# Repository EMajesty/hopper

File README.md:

[STM32H743VI](https://www.st.com/resource/en/datasheet/stm32h743vi.pdf)

[PCM3060](https://www.ti.com/lit/ds/symlink/pcm3060.pdf?ts=1771415639587&ref_url=https%253A%252F%252Fwww.ti.com%252Fproduct%252FPCM3060)

[OPA1652](https://www.ti.com/lit/ds/symlink/opa1652.pdf?ts=1771326899051)

[TPS6216x](https://www.ti.com/lit/ds/symlink/tps62160.pdf?ts=1771423545452&ref_url=https%253A%252F%252Fwww.ti.com%252Fproduct%252FTPS62160)

[AMS1117](http://www.advanced-monolithic.com/pdf/ds1117.pdf)

[Omron G5V-2 relay](https://omronfs.omron.com/en_US/ecb/products/pdf/en-g5v_2.pdf)

[Crystal](https://jlcpcb.com/api/file/downloadByFileSystemAccessId/8588976059073646592)

[Tayda 9mm pot](https://www.taydaelectronics.com/datasheets/A-1859.pdf)

[AN4938 - Hardware development](https://www.st.com/resource/en/application_note/an4938-getting-started-with-stm32h74xig-and-stm32h75xig-mcu-hardware-development-stmicroelectronics.pdf)

[AN2867 - Oscillator design](https://www.st.com/resource/en/application_note/cd00221665-oscillator-design-guide-for-stm8af-al-s-stm32-mcus-and-mpus-stmicroelectronics.pdf)

[AN2606 - Memory boot](https://www.st.com/resource/en/application_note/cd00167594-stm32-microcontroller-system-memory-boot-mode-stmicroelectronics.pdf)

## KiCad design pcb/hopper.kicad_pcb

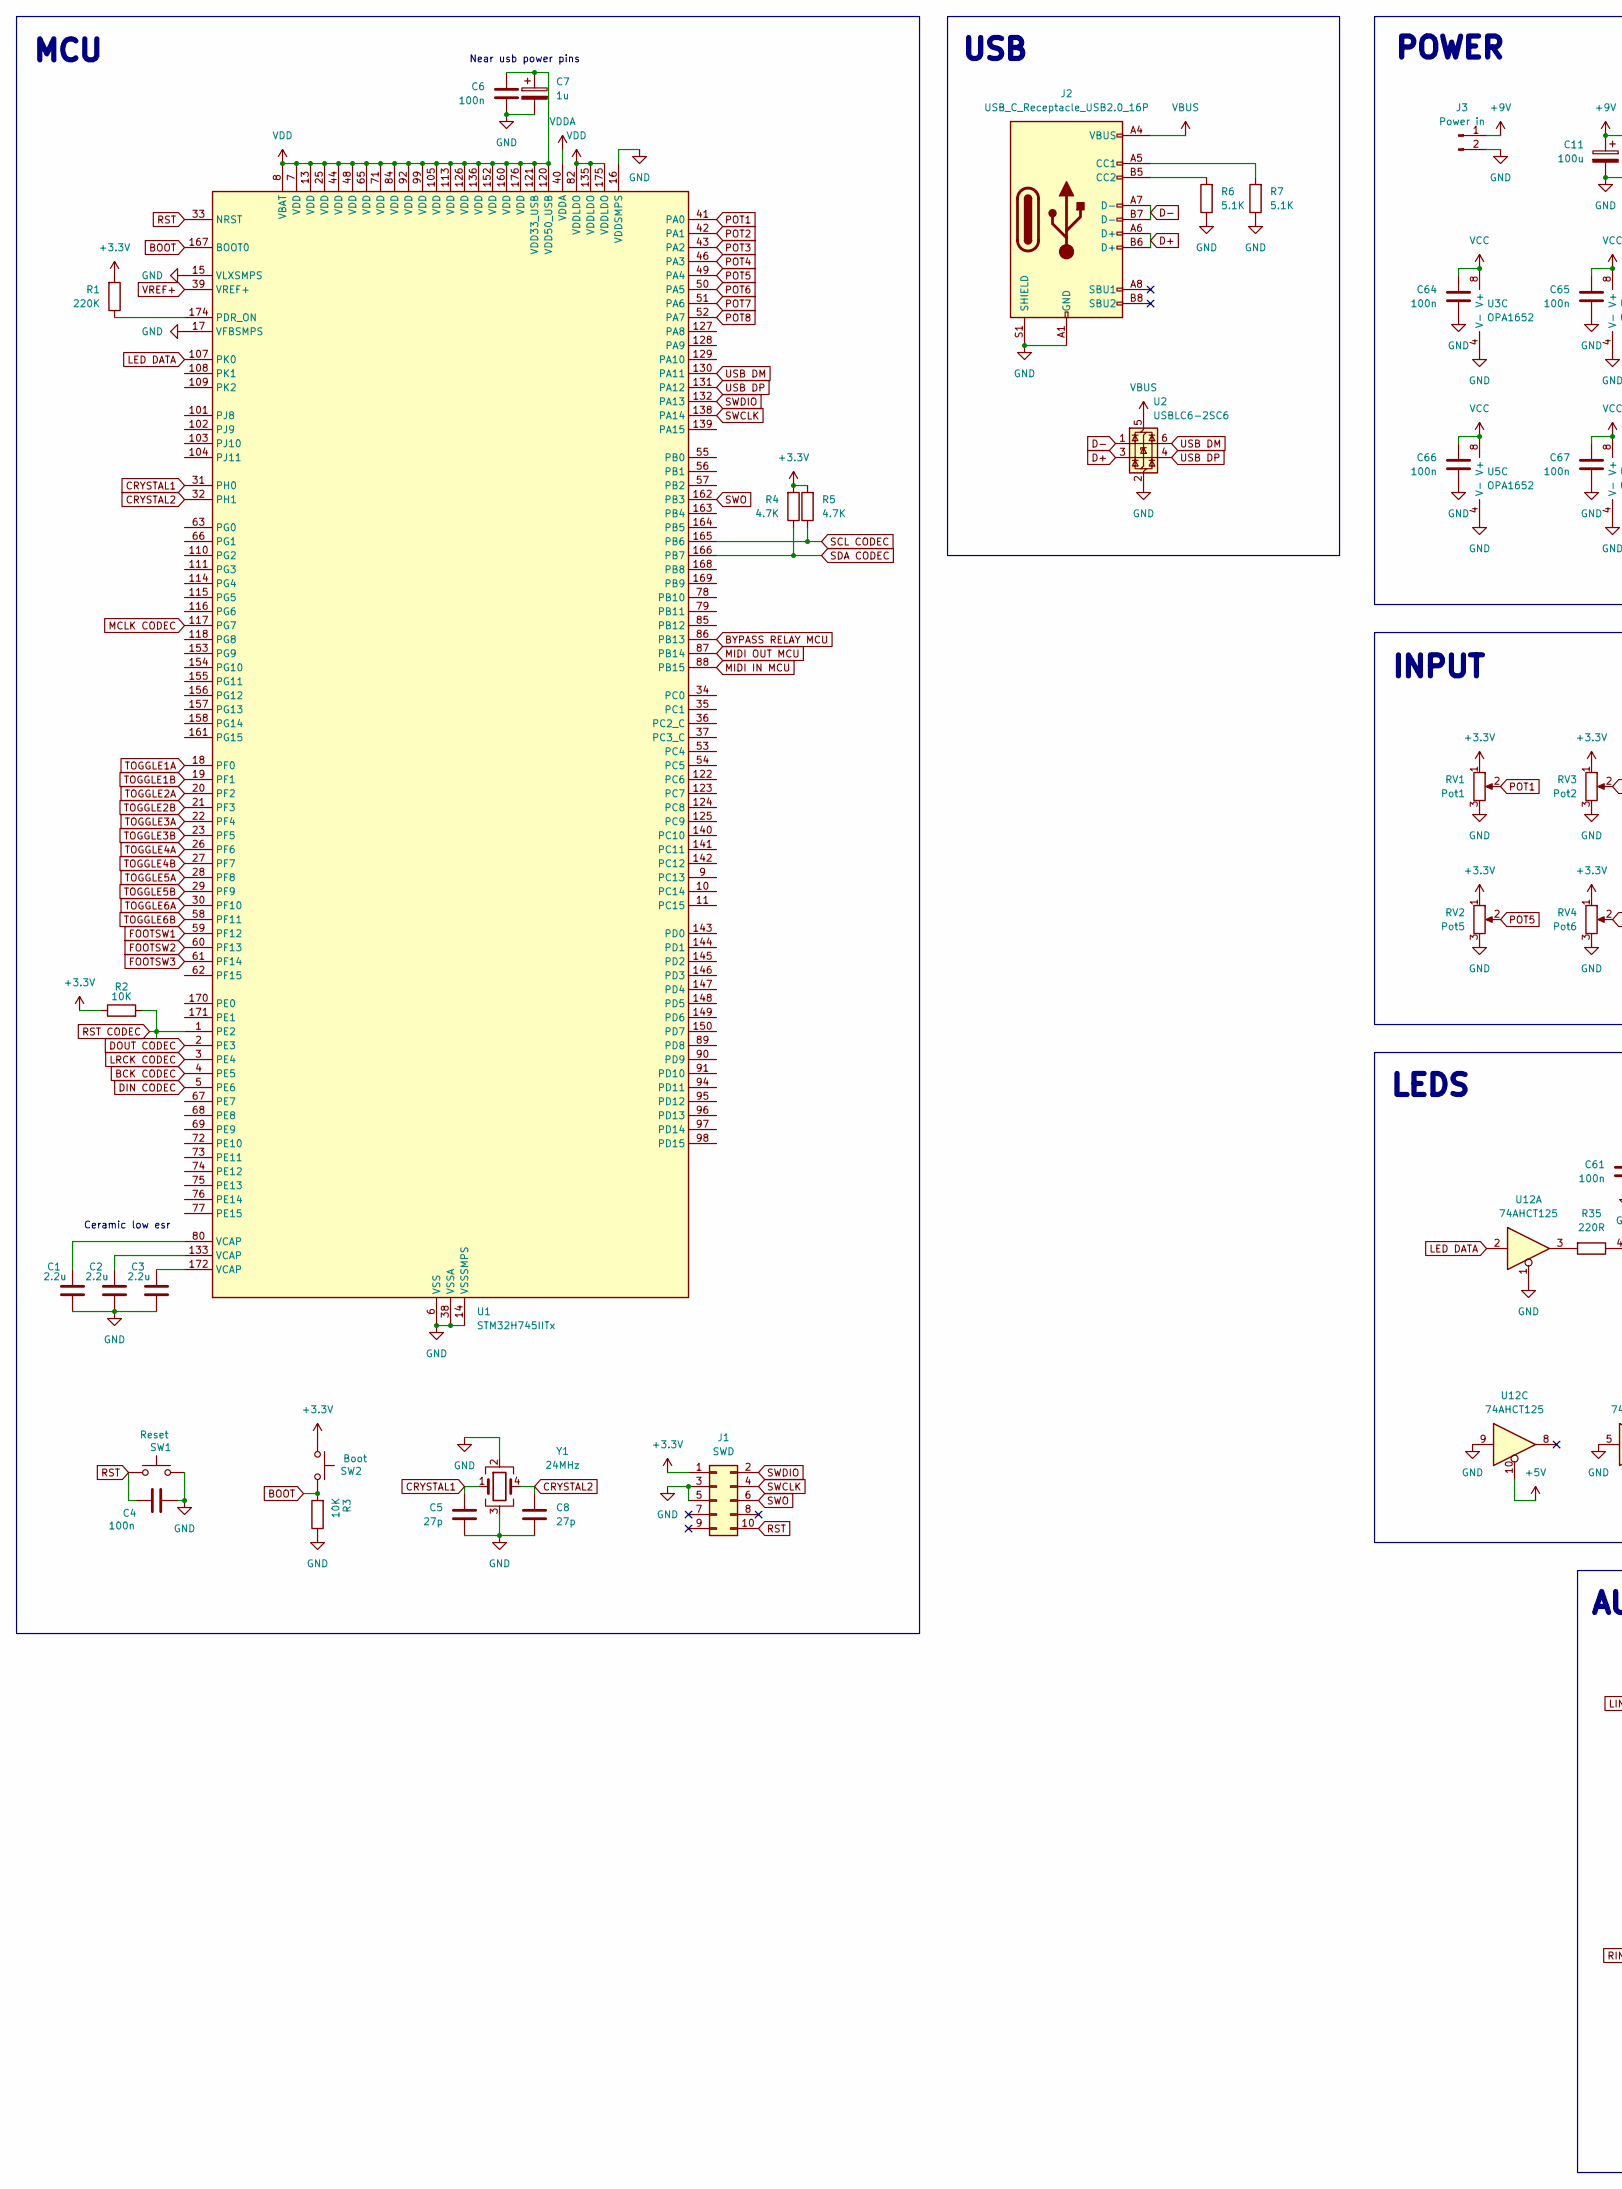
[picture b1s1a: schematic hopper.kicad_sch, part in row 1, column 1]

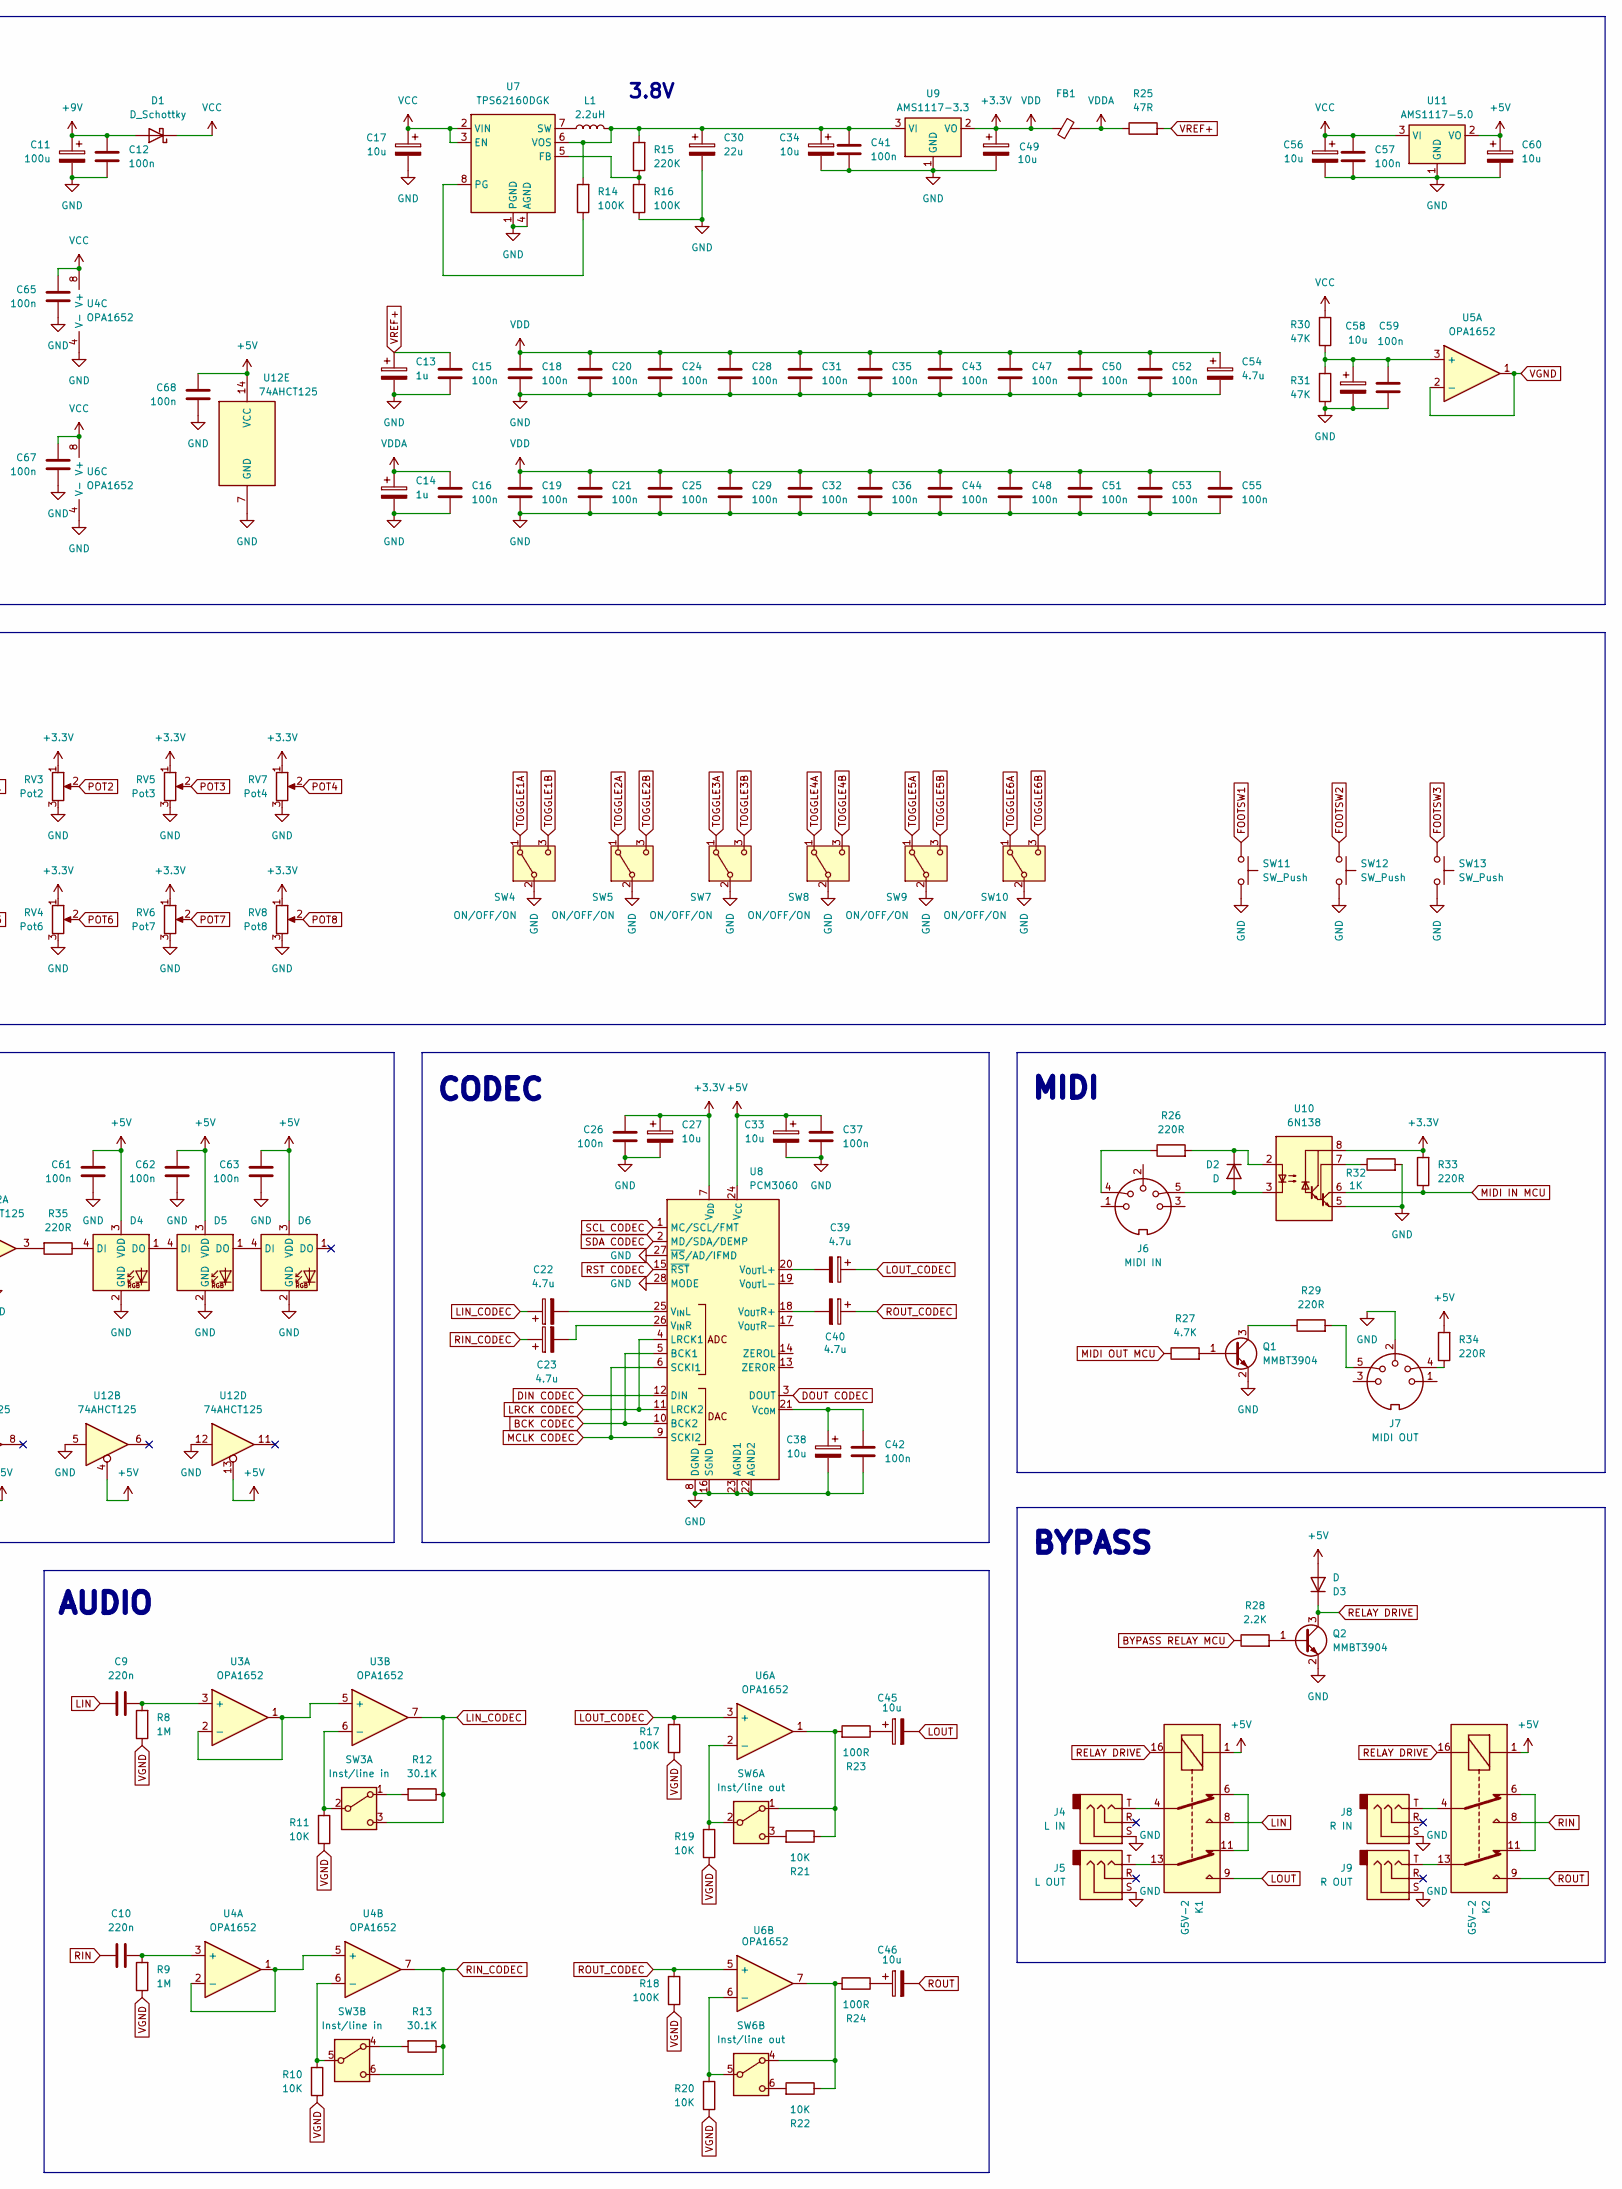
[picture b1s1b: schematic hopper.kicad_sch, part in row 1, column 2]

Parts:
C1, C2, C3: 2.2u; C_0603_1608Metric
C4, C6, C12, C15, C16, C18, C19, C20, C21, C24, C25, C26, C28, C29, C31, C32, C35, C36, C37, C41, C42, C43, C44, C47, C48, C50, C51, C52, C53, C55, C57, C59, C61, C62, C63, C64, C65, C66, C67, C68: 100n; C_0603_1608Metric
C5, C8: 27p; C_0603_1608Metric
C7, C13, C14: 1u; C_0603_1608Metric
C9, C10: 220n; C_0603_1608Metric
C11: 100u; C_0603_1608Metric
C17, C27, C33, C34, C38, C45, C46, C49, C56, C58, C60: 10u; C_0603_1608Metric
C22, C23, C39, C40, C54: 4.7u; C_0603_1608Metric
C30: 22u; C_0805_2012Metric
D1: D_Schottky; D_0603_1608Metric
D2, D3: D; D_0603_1608Metric
D4, D5, D6: APA-106-F5; LED_D5.0mm-4_RGB
FB1: FerriteBead_Small; R_0603_1608Metric
J1: SWD; PinHeader_2x05_P2.54mm_Vertical
J2: USB_C_Receptacle_USB2.0_16P; USB_C_Receptacle_GCT_USB4105-xx-A_16P_TopMnt_Horizontal
J3: Power in; PinHeader_1x02_P2.54mm_Vertical
J4: L IN; Jack_6.35mm_Neutrik_NMJ6HCD2_Horizontal
J5: L OUT; Jack_6.35mm_Neutrik_NMJ6HCD2_Horizontal
J6: MIDI IN
J7: MIDI OUT
J8: R IN; Jack_6.35mm_Neutrik_NMJ6HCD2_Horizontal
J9: R OUT; Jack_6.35mm_Neutrik_NMJ6HCD2_Horizontal
K1, K2: G5V-2; Relay_DPDT_Omron_G5V-2
L1: 2.2uH; R_0603_1608Metric
Q1, Q2: MMBT3904; SOT-23
R1, R15: 220K; R_0603_1608Metric
R2, R3, R10, R11, R19, R20, R21, R22: 10K; R_0603_1608Metric
R4, R5, R27: 4.7K; R_0603_1608Metric
R6, R7: 5.1K; R_0603_1608Metric
R8, R9: 1M; R_0603_1608Metric
R12, R13: 30.1K; R_0603_1608Metric
R14, R16, R17, R18: 100K; R_0603_1608Metric
R23, R24: 100R; R_0603_1608Metric
R25: 47R; R_0603_1608Metric
R26, R29, R33, R34, R35: 220R; R_0603_1608Metric
R28: 2.2K; R_0603_1608Metric
R30, R31: 47K; R_0603_1608Metric
R32: 1K; R_0603_1608Metric
RV1: Pot1; Pot_9mm_DShaft
RV2: Pot5; Pot_9mm_DShaft
RV3: Pot2; Pot_9mm_DShaft
RV4: Pot6; Pot_9mm_DShaft
RV5: Pot3; Pot_9mm_DShaft
RV6: Pot7; Pot_9mm_DShaft
RV7: Pot4; Pot_9mm_DShaft
RV8: Pot8; Pot_9mm_DShaft
SW1: Reset; SW_SPST_TL3342
SW2: Boot; SW_SPST_TL3342
SW3: Inst/line in
SW4, SW5, SW7, SW8, SW9, SW10: ON/OFF/ON; Switch_Toggle_SPDT_Mini_SolderLug
SW6: Inst/line out
SW11, SW12, SW13: SW_Push; PinHeader_1x02_P2.54mm_Vertical
U1: STM32H745IITx; LQFP-176_24x24mm_P0.5mm
U2: USBLC6-2SC6; SOT-23-6
U3, U4, U5, U6: OPA1652; SOIC-8-1EP_3.9x4.9mm_P1.27mm_EP2.29x3mm
U7: TPS62160DGK; MSOP-8_3x3mm_P0.65mm
U8: PCM3060; TSSOP-28_4.4x9.7mm_P0.65mm
U9: AMS1117-3.3; SOT-223-3_TabPin2
U10: 6N138; DIP-8_W7.62mm
U11: AMS1117-5.0; SOT-223-3_TabPin2
U12: 74AHCT125; SOIC-14_3.9x8.7mm_P1.27mm
Y1: 24MHz; Crystal_SMD_3225-4Pin_3.2x2.5mm; JLC C1122380

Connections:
+3.3V: C6.1, C7.1, C18.1, C19.1, C20.1, C21.1, C24.1, C25.1, C26.1, C27.1, C28.1, C29.1, C31.1, C32.1, C35.1, C36.1, C43.1, C44.1, C47.1, C48.1, C49.1, C50.1, C51.1, C52.1, C53.1, C54.1, C55.1, FB1.1, J1.1, R1.2, R2.1, R4.2, R5.2, R33.2, RV1.1, RV2.1, RV3.1, RV4.1, RV5.1, RV6.1, RV7.1, RV8.1, SW2.1, U1.7 (VDD), U1.8 (VBAT), U1.13 (VDD), U1.25 (VDD), U1.44 (VDD), U1.48 (VDD), U1.65 (VDD), U1.71 (VDD), U1.82 (VDDLDO), U1.84 (VDD), U1.92 (VDD), U1.99 (VDD), U1.105 (VDD), U1.113 (VDD), U1.120 (VDD50_USB), U1.121 (VDD33_USB), U1.126 (VDD), U1.135 (VDDLDO), U1.136 (VDD), U1.152 (VDD), U1.160 (VDD), U1.175 (VDDLDO), U1.176 (VDD), U8.7 (V_{DD}), U9.2 (VO), U10.8 (VCC)
+5V: C33.1, C37.1, C60.1, C61.1, C62.1, C63.1, C68.1, D3.2 (A), D4.3 (VDD), D5.3 (VDD), D6.3 (VDD), K1.1, K2.1, R34.2, U8.24 (V_{CC}), U11.2 (VO), U12.4, U12.10, U12.13, U12.14 (VCC)
+9V: C11.1, C12.1, D1.2 (A), J3.1
BCK CODEC: U1.4 (PE5), U8.5 (BCK1), U8.10 (BCK2)
BOOT: R3.2, SW2.2, U1.167 (BOOT0)
BYPASS RELAY MCU: R28.1, U1.86 (PB13)
CRYSTAL1: C5.1, U1.31 (PH0), Y1.1
CRYSTAL2: C8.1, U1.32 (PH1), Y1.4
D+: J2.A6 (D+), J2.B6 (D+), U2.3 (I/O2)
D-: J2.A7 (D-), J2.B7 (D-), U2.1 (I/O1)
DIN CODEC: U1.5 (PE6), U8.12 (DIN)
DOUT CODEC: U1.2 (PE3), U8.3 (DOUT)
FOOTSW1: SW11.1, U1.59 (PF12)
FOOTSW2: SW12.1, U1.60 (PF13)
FOOTSW3: SW13.1, U1.61 (PF14)
GND: C1.2, C2.2, C3.2, C4.2, C5.2, C6.2, C7.2, C8.2, C11.2, C12.2, C13.2, C14.2, C15.2, C16.2, C17.2, C18.2, C19.2, C20.2, C21.2, C24.2, C25.2, C26.2, C27.2, C28.2, C29.2, C30.2, C31.2, C32.2, C33.2, C34.2, C35.2, C36.2, C37.2, C38.2, C41.2, C42.2, C43.2, C44.2, C47.2, C48.2, C49.2, C50.2, C51.2, C52.2, C53.2, C54.2, C55.2, C56.2, C57.2, C58.2, C59.2, C60.2, C61.2, C62.2, C63.2, C64.2, C65.2, C66.2, C67.2, C68.2, D4.2 (GND), D5.2 (GND), D6.2 (GND), J1.3, J1.5, J2.A1 (GND), J2.A12 (GND), J2.B1 (GND), J2.B12 (GND), J2.S1 (SHIELD), J3.2, J4.S, J5.S, J7.2, J8.S, J9.S, Q1.2 (E), Q2.2 (E), R3.1, R6.1, R7.1, R16.1, R31.1, R32.2, RV1.3, RV2.3, RV3.3, RV4.3, RV5.3, RV6.3, RV7.3, RV8.3, SW1.1, SW4.2 (B), SW5.2 (B), SW7.2 (B), SW8.2 (B), SW9.2 (B), SW10.2 (B), SW11.2, SW12.2, SW13.2, U1.6 (VSS), U1.12 (VSS), U1.14 (VSSSMPS), U1.15 (VLXSMPS), U1.16 (VDDSMPS), U1.17 (VFBSMPS), U1.24 (VSS), U1.38 (VSSA), U1.45 (VSS), U1.47 (VSS), U1.64 (VSS), U1.70 (VSS), U1.81 (VSS), U1.83 (VSS), U1.93 (VSS), U1.100 (VSS), U1.106 (VSS), U1.112 (VSS), U1.119 (VSS), U1.134 (VSS), U1.137 (VSS), U1.151 (VSS), U1.159 (VSS), U1.173 (VSS), U2.2 (GND), U3.4 (V-), U4.4 (V-), U5.4 (V-), U6.4 (V-), U7.1 (PGND), U7.4 (AGND), U8.8 (DGND), U8.16 (SGND), U8.22 (AGND2), U8.23 (AGND1), U8.27 (~MS/AD/IFMD), U8.28 (MODE), U9.1 (GND), U10.5 (GND), U11.1 (GND), U12.1, U12.5, U12.7 (GND), U12.9, U12.12, Y1.2, Y1.3
LED DATA: U1.107 (PK0), U12.2
LIN: C9.1, K1.8
LIN_CODEC: C22.1, R12.1, SW3.3 (C), U3.7
LOUT: C45.2, K1.9
LOUT_CODEC: C39.1, R17.2, U6.3 (+)
LRCK CODEC: U1.3 (PE4), U8.4 (LRCK1), U8.11 (LRCK2)
MCLK CODEC: U1.117 (PG7), U8.6 (SCKI1), U8.9 (SCKI2)
MIDI IN MCU: R33.1, U1.88 (PB15), U10.6 (VO2)
MIDI OUT MCU: R27.1, U1.87 (PB14)
unnamed: C1.1, U1.80 (VCAP)
unnamed: C2.1, U1.133 (VCAP)
unnamed: C3.1, U1.172 (VCAP)
unnamed: C45.1, R23.1
unnamed: C46.1, R24.1
unnamed: D2.2 (A), J6.5, U10.3 (C2)
unnamed: D2.1 (K), R26.2, U10.2 (C1)
unnamed: D4.4 (DI), R35.1
unnamed: D4.1 (DO), D5.4 (DI)
unnamed: D5.1 (DO), D6.4 (DI)
unnamed: J2.A5 (CC1), R7.2
unnamed: J2.B5 (CC2), R6.2
unnamed: J4.T, K1.4
unnamed: J5.T, K1.13
unnamed: J6.4, R26.1
unnamed: J7.4, R34.1
unnamed: J7.5, R29.2
unnamed: J8.T, K2.4
unnamed: J9.T, K2.13
unnamed: K1.6, K1.11
unnamed: K2.6, K2.11
unnamed: Q1.1 (B), R27.2
unnamed: Q1.3 (C), R29.1
unnamed: Q2.1 (B), R28.2
unnamed: R35.2, U12.3
unnamed: R12.2, SW3.1 (A)
unnamed: R11.2, SW3.2 (B), U3.6 (-)
unnamed: R13.2, SW3.4 (A)
unnamed: R10.2, SW3.5 (B), U4.6 (-)
unnamed: R21.1, R23.2, SW6.1 (A), U6.1
unnamed: R19.2, SW6.2 (B), U6.2 (-)
unnamed: R21.2, SW6.3 (C)
unnamed: R22.1, R24.2, SW6.4 (A), U6.7
unnamed: R20.2, SW6.5 (B), U6.6 (-)
unnamed: R22.2, SW6.6 (C)
unnamed: R1.1, U1.174 (PDR_ON)
unnamed: C9.2, R8.2, U3.3 (+)
unnamed: U3.1, U3.2 (-), U3.5 (+)
unnamed: C10.2, R9.2, U4.3 (+)
unnamed: U4.1, U4.2 (-), U4.5 (+)
unnamed: C58.1, C59.1, R30.1, R31.2, U5.3 (+)
unnamed: R15.1, R16.2, U7.5 (FB)
unnamed: R14.1, U7.8 (PG)
unnamed: L1.1, U7.7 (SW)
unnamed: C30.1, C34.1, C41.1, L1.2, R14.2, R15.2, U7.6 (VOS), U9.3 (VI)
unnamed: C38.1, C42.1, U8.21 (V_{COM})
unnamed: C22.2, U8.25 (V_{IN}L)
unnamed: C23.2, U8.26 (V_{IN}R)
unnamed: C39.2, U8.20 (V_{OUT}L+)
unnamed: C40.2, U8.18 (V_{OUT}R+)
unnamed: R32.1, U10.7 (VO1)
POT1: RV1.2, U1.41 (PA0)
POT2: RV3.2, U1.42 (PA1)
POT3: RV5.2, U1.43 (PA2)
POT4: RV7.2, U1.46 (PA3)
POT5: RV2.2, U1.49 (PA4)
POT6: RV4.2, U1.50 (PA5)
POT7: RV6.2, U1.51 (PA6)
POT8: RV8.2, U1.52 (PA7)
RELAY DRIVE: D3.1 (K), K1.16, K2.16, Q2.3 (C)
RIN: C10.1, K2.8
RIN_CODEC: C23.1, R13.1, SW3.6 (C), U4.7
ROUT: C46.2, K2.9
ROUT_CODEC: C40.1, R18.2, U6.5 (+)
RST: C4.1, J1.10, SW1.2, U1.33 (NRST)
RST CODEC: R2.2, U1.1 (PE2), U8.15 (~RST)
SCL CODEC: R5.1, U1.165 (PB6), U8.1 (MC/SCL/FMT)
SDA CODEC: R4.1, U1.166 (PB7), U8.2 (MD/SDA/DEMP)
SWCLK: J1.4, U1.138 (PA14)
SWDIO: J1.2, U1.132 (PA13)
SWO: J1.6, U1.162 (PB3)
TOGGLE1A: SW4.1 (A), U1.18 (PF0)
TOGGLE1B: SW4.3 (C), U1.19 (PF1)
TOGGLE2A: SW5.1 (A), U1.20 (PF2)
TOGGLE2B: SW5.3 (C), U1.21 (PF3)
TOGGLE3A: SW7.1 (A), U1.22 (PF4)
TOGGLE3B: SW7.3 (C), U1.23 (PF5)
TOGGLE4A: SW8.1 (A), U1.26 (PF6)
TOGGLE4B: SW8.3 (C), U1.27 (PF7)
TOGGLE5A: SW9.1 (A), U1.28 (PF8)
TOGGLE5B: SW9.3 (C), U1.29 (PF9)
TOGGLE6A: SW10.1 (A), U1.30 (PF10)
TOGGLE6B: SW10.3 (C), U1.58 (PF11)
USB DM: U1.130 (PA11), U2.6 (I/O1)
USB DP: U1.131 (PA12), U2.4 (I/O2)
VBUS: J2.A4 (VBUS), J2.A9 (VBUS), J2.B4 (VBUS), J2.B9 (VBUS), U2.5 (VBUS)
VCC: C17.1, C56.1, C57.1, C64.1, C65.1, C66.1, C67.1, D1.1 (K), R30.2, U3.8 (V+), U4.8 (V+), U5.8 (V+), U6.8 (V+), U7.2 (VIN), U7.3 (EN), U11.3 (VI)
VDDA: C14.1, C16.1, FB1.2, R25.1, U1.40 (VDDA)
VGND: R8.1, R9.1, R10.1, R11.1, R17.1, R18.1, R19.1, R20.1, U5.1, U5.2 (-)
VREF+: C13.1, C15.1, R25.2, U1.39 (VREF+)

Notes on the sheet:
Near usb power pins
MIDI
MCU
INPUT
POWER
CODEC
AUDIO
BYPASS
3.8V
Ceramic low esr
USB
LEDS

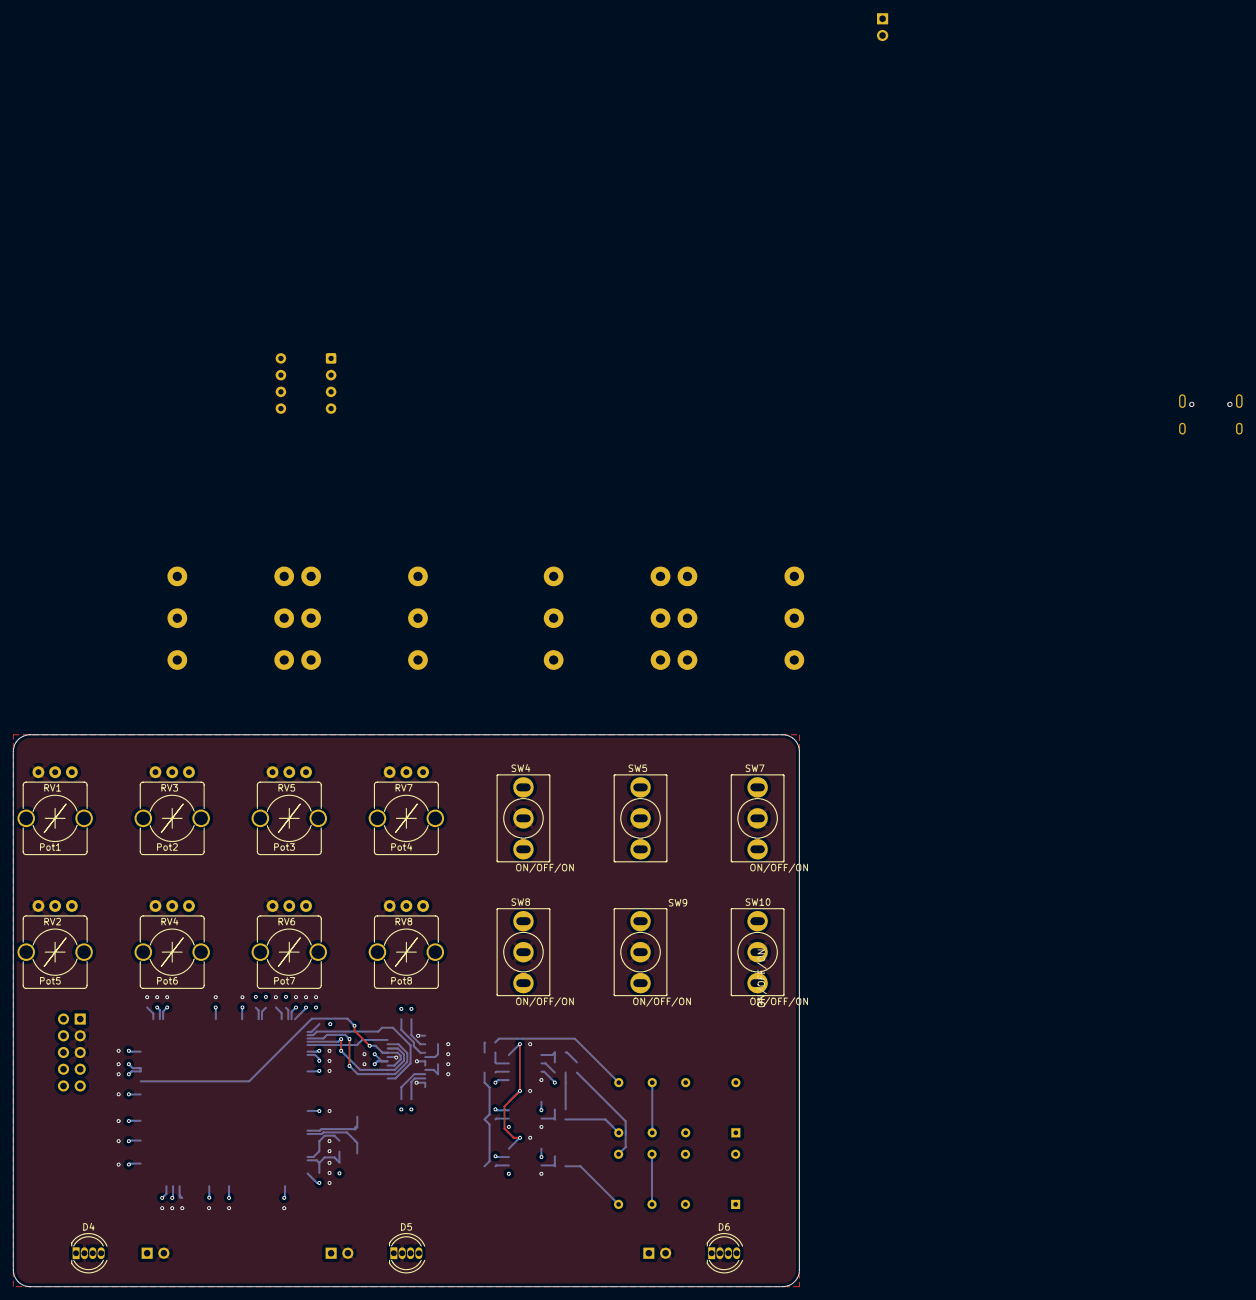
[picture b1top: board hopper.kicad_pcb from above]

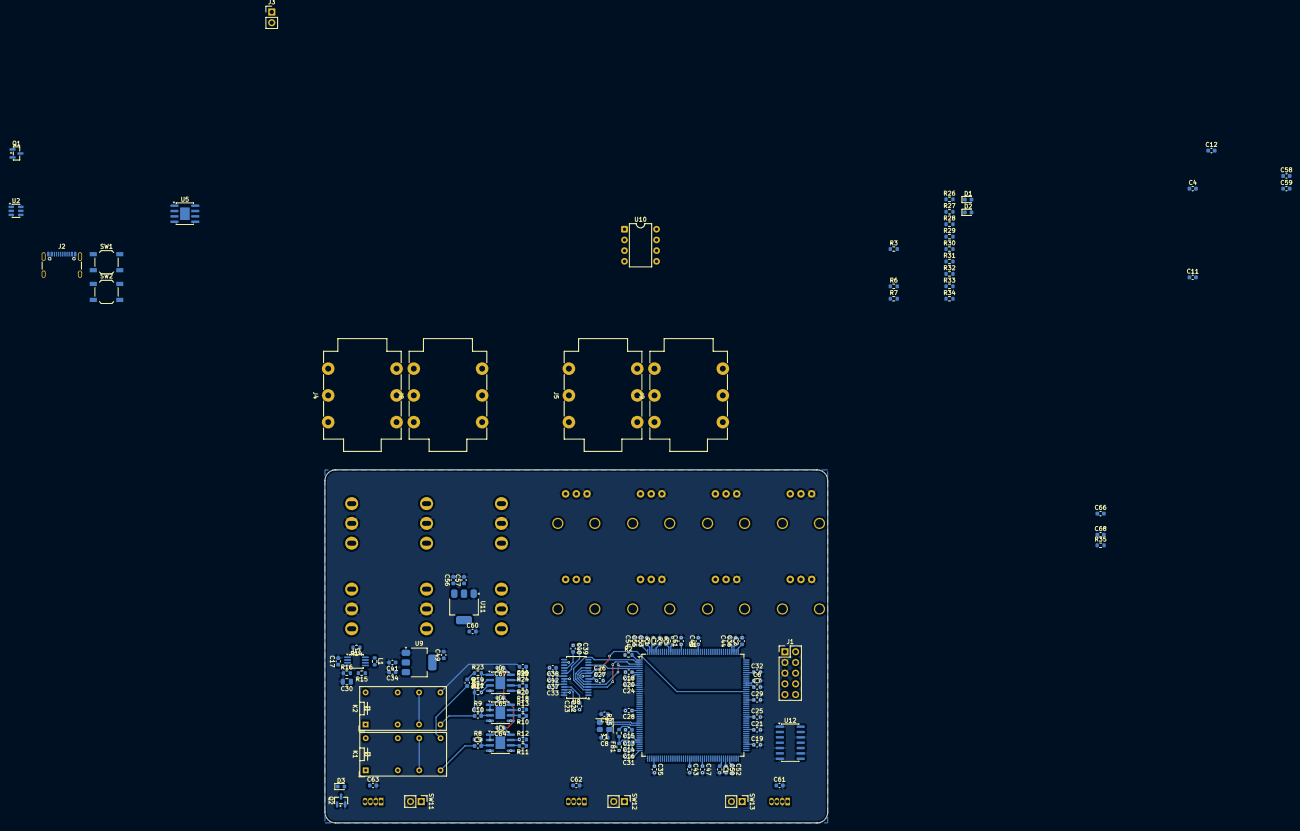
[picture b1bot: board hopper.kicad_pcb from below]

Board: 4 copper layers, 119.4 x 83.8 mm, 154 parts (137 on the bottom side), 108 nets.

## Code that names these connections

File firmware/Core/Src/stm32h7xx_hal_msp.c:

/* USER CODE BEGIN Header */
/**
  ******************************************************************************
  * @file         stm32h7xx_hal_msp.c
  * @brief        This file provides code for the MSP Initialization
  *               and de-Initialization codes.
  ******************************************************************************
  * @attention
  *
  * Copyright (c) 2026 STMicroelectronics.
  * All rights reserved.
  *
  * This software is licensed under terms that can be found in the LICENSE file
  * in the root directory of this software component.
  * If no LICENSE file comes with this software, it is provided AS-IS.
  *
  ******************************************************************************
  */
/* USER CODE END Header */
/* Includes ------------------------------------------------------------------*/
#include "main.h"
/* USER CODE BEGIN Includes */

/* USER CODE END Includes */

/* Private typedef -----------------------------------------------------------*/
/* USER CODE BEGIN TD */

/* USER CODE END TD */

/* Private define ------------------------------------------------------------*/
/* USER CODE BEGIN Define */

/* USER CODE END Define */

/* Private macro -------------------------------------------------------------*/
/* USER CODE BEGIN Macro */

/* USER CODE END Macro */

/* Private variables ---------------------------------------------------------*/
/* USER CODE BEGIN PV */

/* USER CODE END PV */

/* Private function prototypes -----------------------------------------------*/
/* USER CODE BEGIN PFP */

/* USER CODE END PFP */

/* External functions --------------------------------------------------------*/
/* USER CODE BEGIN ExternalFunctions */

/* USER CODE END ExternalFunctions */

/* USER CODE BEGIN 0 */

/* USER CODE END 0 */
/**
  * Initializes the Global MSP.
  */
void HAL_MspInit(void)
{

  /* USER CODE BEGIN MspInit 0 */

  /* USER CODE END MspInit 0 */

  __HAL_RCC_SYSCFG_CLK_ENABLE();

  /* System interrupt init*/

  /* USER CODE BEGIN MspInit 1 */

  /* USER CODE END MspInit 1 */
}

/**
  * @brief ADC MSP Initialization
  * This function configures the hardware resources used in this example
  * @param hadc: ADC handle pointer
  * @retval None
  */
void HAL_ADC_MspInit(ADC_HandleTypeDef* hadc)
{
  GPIO_InitTypeDef GPIO_InitStruct = {0};
  RCC_PeriphCLKInitTypeDef PeriphClkInitStruct = {0};
  if(hadc->Instance==ADC1)
  {
    /* USER CODE BEGIN ADC1_MspInit 0 */

    /* USER CODE END ADC1_MspInit 0 */

  /** Initializes the peripherals clock
  */
    PeriphClkInitStruct.PeriphClockSelection = RCC_PERIPHCLK_ADC;
    PeriphClkInitStruct.PLL2.PLL2M = 2;
    PeriphClkInitStruct.PLL2.PLL2N = 40;
    PeriphClkInitStruct.PLL2.PLL2P = 6;
    PeriphClkInitStruct.PLL2.PLL2Q = 2;
    PeriphClkInitStruct.PLL2.PLL2R = 2;
    PeriphClkInitStruct.PLL2.PLL2RGE = RCC_PLL2VCIRANGE_3;
    PeriphClkInitStruct.PLL2.PLL2VCOSEL = RCC_PLL2VCOWIDE;
    PeriphClkInitStruct.PLL2.PLL2FRACN = 0.0;
    PeriphClkInitStruct.AdcClockSelection = RCC_ADCCLKSOURCE_PLL2;
    if (HAL_RCCEx_PeriphCLKConfig(&PeriphClkInitStruct) != HAL_OK)
    {
      Error_Handler();
    }

    /* Peripheral clock enable */
    __HAL_RCC_ADC12_CLK_ENABLE();

    __HAL_RCC_GPIOC_CLK_ENABLE();
    __HAL_RCC_GPIOA_CLK_ENABLE();
    __HAL_RCC_GPIOB_CLK_ENABLE();
    /**ADC1 GPIO Configuration
    PC0     ------> ADC1_INP10
    PC1     ------> ADC1_INP11
    PA0     ------> ADC1_INP16
    PA1     ------> ADC1_INP17
    PA2     ------> ADC1_INP14
    PA3     ------> ADC1_INP15
    PA4     ------> ADC1_INP18
    PA5     ------> ADC1_INP19
    PA6     ------> ADC1_INP3
    PA7     ------> ADC1_INP7
    PC4     ------> ADC1_INP4
    PC5     ------> ADC1_INP8
    PB0     ------> ADC1_INP9
    PB1     ------> ADC1_INP5
    */
    GPIO_InitStruct.Pin = GPIO_PIN_0|GPIO_PIN_1|GPIO_PIN_4|GPIO_PIN_5;
    GPIO_InitStruct.Mode = GPIO_MODE_ANALOG;
    GPIO_InitStruct.Pull = GPIO_PULLDOWN;
    HAL_GPIO_Init(GPIOC, &GPIO_InitStruct);

    GPIO_InitStruct.Pin = GPIO_PIN_0|GPIO_PIN_1|GPIO_PIN_2|GPIO_PIN_3
                          |GPIO_PIN_4|GPIO_PIN_5|GPIO_PIN_6|GPIO_PIN_7;
    GPIO_InitStruct.Mode = GPIO_MODE_ANALOG;
    GPIO_InitStruct.Pull = GPIO_NOPULL;
    HAL_GPIO_Init(GPIOA, &GPIO_InitStruct);

    GPIO_InitStruct.Pin = GPIO_PIN_0|GPIO_PIN_1;
    GPIO_InitStruct.Mode = GPIO_MODE_ANALOG;
    GPIO_InitStruct.Pull = GPIO_PULLDOWN;
    HAL_GPIO_Init(GPIOB, &GPIO_InitStruct);

    /* USER CODE BEGIN ADC1_MspInit 1 */

    /* USER CODE END ADC1_MspInit 1 */

  }

}

/**
  * @brief ADC MSP De-Initialization
  * This function freeze the hardware resources used in this example
  * @param hadc: ADC handle pointer
  * @retval None
  */
void HAL_ADC_MspDeInit(ADC_HandleTypeDef* hadc)
{
  if(hadc->Instance==ADC1)
  {
    /* USER CODE BEGIN ADC1_MspDeInit 0 */

    /* USER CODE END ADC1_MspDeInit 0 */
    /* Peripheral clock disable */
    __HAL_RCC_ADC12_CLK_DISABLE();

    /**ADC1 GPIO Configuration
    PC0     ------> ADC1_INP10
    PC1     ------> ADC1_INP11
    PA0     ------> ADC1_INP16
    PA1     ------> ADC1_INP17
    PA2     ------> ADC1_INP14
    PA3     ------> ADC1_INP15
    PA4     ------> ADC1_INP18
    PA5     ------> ADC1_INP19
    PA6     ------> ADC1_INP3
    PA7     ------> ADC1_INP7
    PC4     ------> ADC1_INP4
    PC5     ------> ADC1_INP8
    PB0     ------> ADC1_INP9
    PB1     ------> ADC1_INP5
    */
    HAL_GPIO_DeInit(GPIOC, GPIO_PIN_0|GPIO_PIN_1|GPIO_PIN_4|GPIO_PIN_5);

    HAL_GPIO_DeInit(GPIOA, GPIO_PIN_0|GPIO_PIN_1|GPIO_PIN_2|GPIO_PIN_3
                          |GPIO_PIN_4|GPIO_PIN_5|GPIO_PIN_6|GPIO_PIN_7);

    HAL_GPIO_DeInit(GPIOB, GPIO_PIN_0|GPIO_PIN_1);

    /* USER CODE BEGIN ADC1_MspDeInit 1 */

    /* USER CODE END ADC1_MspDeInit 1 */
  }

}

static uint32_t SAI1_client =0;

void HAL_SAI_MspInit(SAI_HandleTypeDef* hsai)
{

  GPIO_InitTypeDef GPIO_InitStruct;
/* SAI1 */
    if(hsai->Instance==SAI1_Block_A)
    {
    /* Peripheral clock enable */
    if (SAI1_client == 0)
    {
       __HAL_RCC_SAI1_CLK_ENABLE();
    }
    SAI1_client ++;

    /**SAI1_A_Block_A GPIO Configuration
    PE2     ------> SAI1_MCLK_A
    PE4     ------> SAI1_FS_A
    PE5     ------> SAI1_SCK_A
    PE6     ------> SAI1_SD_A
    */
    GPIO_InitStruct.Pin = GPIO_PIN_2|GPIO_PIN_4|GPIO_PIN_5|GPIO_PIN_6;
    GPIO_InitStruct.Mode = GPIO_MODE_AF_PP;
    GPIO_InitStruct.Pull = GPIO_NOPULL;
    GPIO_InitStruct.Speed = GPIO_SPEED_FREQ_LOW;
    GPIO_InitStruct.Alternate = GPIO_AF6_SAI1;
    HAL_GPIO_Init(GPIOE, &GPIO_InitStruct);

    }
    if(hsai->Instance==SAI1_Block_B)
    {
      /* Peripheral clock enable */
      if (SAI1_client == 0)
      {
       __HAL_RCC_SAI1_CLK_ENABLE();
      }
    SAI1_client ++;

    /**SAI1_B_Block_B GPIO Configuration
    PE3     ------> SAI1_SD_B
    */
    GPIO_InitStruct.Pin = GPIO_PIN_3;
    GPIO_InitStruct.Mode = GPIO_MODE_AF_PP;
    GPIO_InitStruct.Pull = GPIO_NOPULL;
    GPIO_InitStruct.Speed = GPIO_SPEED_FREQ_LOW;
    GPIO_InitStruct.Alternate = GPIO_AF6_SAI1;
    HAL_GPIO_Init(GPIOE, &GPIO_InitStruct);

    }
}

void HAL_SAI_MspDeInit(SAI_HandleTypeDef* hsai)
{
/* SAI1 */
    if(hsai->Instance==SAI1_Block_A)
    {
    SAI1_client --;
    if (SAI1_client == 0)
      {
      /* Peripheral clock disable */
       __HAL_RCC_SAI1_CLK_DISABLE();
      }

    /**SAI1_A_Block_A GPIO Configuration
    PE2     ------> SAI1_MCLK_A
    PE4     ------> SAI1_FS_A
    PE5     ------> SAI1_SCK_A
    PE6     ------> SAI1_SD_A
    */
    HAL_GPIO_DeInit(GPIOE, GPIO_PIN_2|GPIO_PIN_4|GPIO_PIN_5|GPIO_PIN_6);

    }
    if(hsai->Instance==SAI1_Block_B)
    {
    SAI1_client --;
      if (SAI1_client == 0)
      {
      /* Peripheral clock disable */
      __HAL_RCC_SAI1_CLK_DISABLE();
      }

    /**SAI1_B_Block_B GPIO Configuration
    PE3     ------> SAI1_SD_B
    */
    HAL_GPIO_DeInit(GPIOE, GPIO_PIN_3);

    }
}

/* USER CODE BEGIN 1 */

/* USER CODE END 1 */

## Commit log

2026-02-17 init
2026-02-17 links
2026-02-17 stuff
2026-06-19 Add nix-direnv environment and flake profile configuration
2026-06-19 Add ADC1 channel configuration and GPIO pin assignments to STM32 IOC
2026-06-20 Add I2C4 peripheral, configure ADC pull-downs, and update PLL2 clocks
2026-06-20 Remove STM32CubeMX-generated firmware source and driver files
2026-06-20 Add STM32CubeMX-generated firmware sources, HAL drivers, and CMake build system
